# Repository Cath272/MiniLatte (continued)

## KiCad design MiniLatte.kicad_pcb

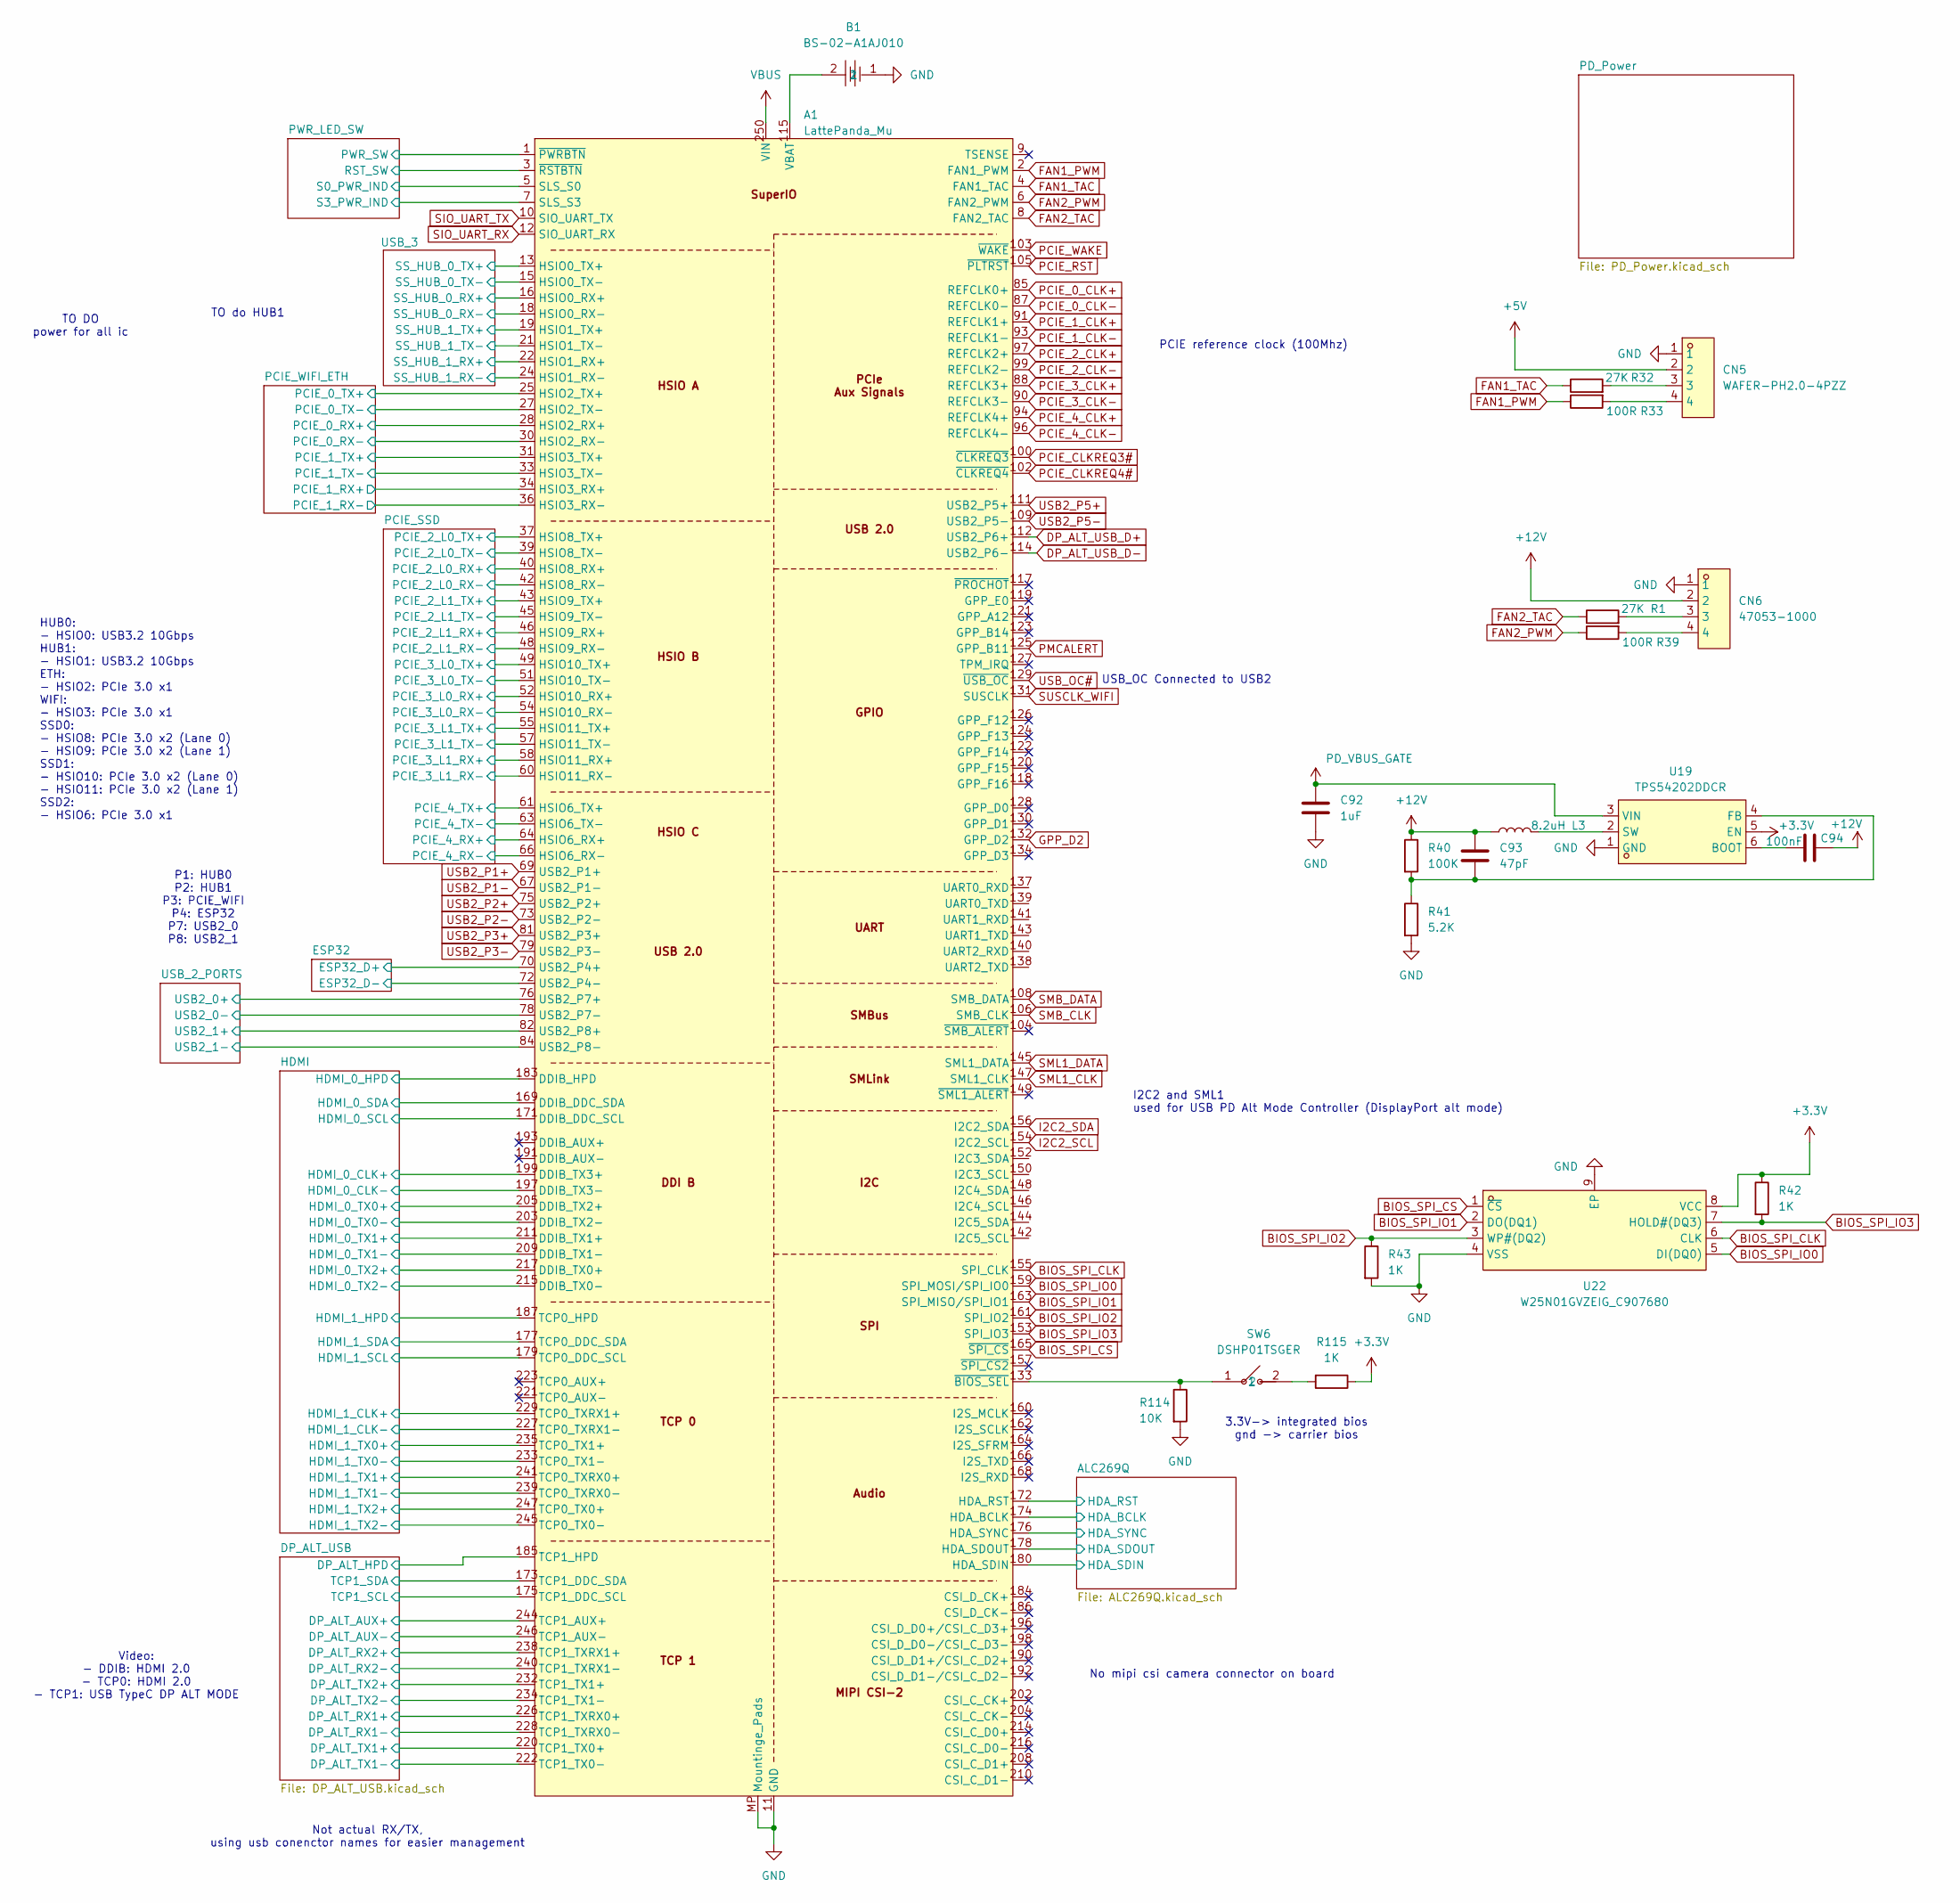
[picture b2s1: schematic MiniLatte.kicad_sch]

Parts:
A1: LattePanda_Mu; LattePanda_Module_H8.0mm_Horizontal
B1: BS-02-A1AJ010; BAT-TH_BS-02-A1AJ010; LCSC Part C5239862
C92: 1uF; C_0603_1608Metric
C93: 47pF; C_0402_1005Metric
C94: 100nF; C_0402_1005Metric
CN5: WAFER-PH2.0-4PZZ; CONN-TH_4P-P2.00_FWF20001-S04S22W5B; LCSC Part C5359601
CN6: 47053-1000; CONN-TH_47053-1000; LCSC Part C240840
L3: 8.2uH; L_Changjiang_FXL0420
R1, R32: 27K; R_0402_1005Metric
R33, R39: 100R; R_0402_1005Metric
R40: 100K; R_0402_1005Metric
R41: 5.2K; R_0402_1005Metric
R42, R43, R115: 1K; R_0402_1005Metric
R114: 10K; R_0402_1005Metric
SW6: DSHP01TSGER; SW-SMD_DSHP01TSGER; LCSC Part C3293141
U19: TPS54202DDCR; SOT-23-6_L2.9-W1.6-P0.95-LS2.8-BL; LCSC Part C191884
U22: W25N01GVZEIG_C907680; WSON-8_L8.0-W6.10-P1.27-BL-EP; LCSC Part C907680

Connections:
+3.3V: R42.1, R115.1, U19.5 (EN), U22.8 (VCC); also elsewhere on the board
+5V: CN5.2; also elsewhere on the board
+12V: C93.1, C94.2, CN6.2, L3.1, R40.1
/ALC269Q/HDA_BCLK: A1.174 (HDA_BCLK); also elsewhere on the board
/ALC269Q/HDA_RST: A1.172 (HDA_RST); also elsewhere on the board
/ALC269Q/HDA_SDIN: A1.180 (HDA_SDIN); also elsewhere on the board
/ALC269Q/HDA_SDOUT: A1.178 (HDA_SDOUT); also elsewhere on the board
/ALC269Q/HDA_SYNC: A1.176 (HDA_SYNC); also elsewhere on the board
/DP_ALT_USB/DP_ALT_HPD: A1.185 (TCP1_HPD); also elsewhere on the board
/DP_ALT_USB/DP_ALT_RX1+: A1.226 (TCP1_TXRX0+); also elsewhere on the board
/DP_ALT_USB/DP_ALT_RX1-: A1.228 (TCP1_TXRX0-); also elsewhere on the board
/DP_ALT_USB/DP_ALT_RX2+: A1.238 (TCP1_TXRX1+); also elsewhere on the board
/DP_ALT_USB/DP_ALT_RX2-: A1.240 (TCP1_TXRX1-); also elsewhere on the board
/DP_ALT_USB/DP_ALT_TX1+: A1.220 (TCP1_TX0+); also elsewhere on the board
/DP_ALT_USB/DP_ALT_TX1-: A1.222 (TCP1_TX0-); also elsewhere on the board
/DP_ALT_USB/DP_ALT_TX2+: A1.232 (TCP1_TX1+); also elsewhere on the board
/DP_ALT_USB/DP_ALT_TX2-: A1.234 (TCP1_TX1-); also elsewhere on the board
/DP_ALT_USB/SBU1: A1.244 (TCP1_AUX+); also elsewhere on the board
/DP_ALT_USB/SBU2: A1.246 (TCP1_AUX-); also elsewhere on the board
/DP_ALT_USB/TCP1_SCL: A1.175 (TCP1_DDC_SCL); also elsewhere on the board
/DP_ALT_USB/TCP1_SDA: A1.173 (TCP1_DDC_SDA); also elsewhere on the board
/ESP32/ESP32_D+: A1.70 (USB2_P4+); also elsewhere on the board
/ESP32/ESP32_D-: A1.72 (USB2_P4-); also elsewhere on the board
/HDMI/HDMI_0_CLK+: A1.199 (DDIB_TX3+); also elsewhere on the board
/HDMI/HDMI_0_CLK-: A1.197 (DDIB_TX3-); also elsewhere on the board
/HDMI/HDMI_0_HPD: A1.183 (DDIB_HPD); also elsewhere on the board
/HDMI/HDMI_0_SCL: A1.171 (DDIB_DDC_SCL); also elsewhere on the board
/HDMI/HDMI_0_SDA: A1.169 (DDIB_DDC_SDA); also elsewhere on the board
/HDMI/HDMI_0_TX0+: A1.205 (DDIB_TX2+); also elsewhere on the board
/HDMI/HDMI_0_TX0-: A1.203 (DDIB_TX2-); also elsewhere on the board
/HDMI/HDMI_0_TX1+: A1.211 (DDIB_TX1+); also elsewhere on the board
/HDMI/HDMI_0_TX1-: A1.209 (DDIB_TX1-); also elsewhere on the board
/HDMI/HDMI_0_TX2+: A1.217 (DDIB_TX0+); also elsewhere on the board
/HDMI/HDMI_0_TX2-: A1.215 (DDIB_TX0-); also elsewhere on the board
/HDMI/HDMI_1_CLK+: A1.229 (TCP0_TXRX1+); also elsewhere on the board
/HDMI/HDMI_1_CLK-: A1.227 (TCP0_TXRX1-); also elsewhere on the board
/HDMI/HDMI_1_HPD: A1.187 (TCP0_HPD); also elsewhere on the board
/HDMI/HDMI_1_SCL: A1.179 (TCP0_DDC_SCL); also elsewhere on the board
/HDMI/HDMI_1_SDA: A1.177 (TCP0_DDC_SDA); also elsewhere on the board
/HDMI/HDMI_1_TX0+: A1.235 (TCP0_TX1+); also elsewhere on the board
/HDMI/HDMI_1_TX0-: A1.233 (TCP0_TX1-); also elsewhere on the board
/HDMI/HDMI_1_TX1+: A1.241 (TCP0_TXRX0+); also elsewhere on the board
/HDMI/HDMI_1_TX1-: A1.239 (TCP0_TXRX0-); also elsewhere on the board
/HDMI/HDMI_1_TX2+: A1.247 (TCP0_TX0+); also elsewhere on the board
/HDMI/HDMI_1_TX2-: A1.245 (TCP0_TX0-); also elsewhere on the board
/PCIE_SSD/PCIE_2_L0_RX+: A1.40 (HSIO8_RX+); also elsewhere on the board
/PCIE_SSD/PCIE_2_L0_RX-: A1.42 (HSIO8_RX-); also elsewhere on the board
/PCIE_SSD/PCIE_2_L0_TX+: A1.37 (HSIO8_TX+); also elsewhere on the board
/PCIE_SSD/PCIE_2_L0_TX-: A1.39 (HSIO8_TX-); also elsewhere on the board
/PCIE_SSD/PCIE_2_L1_RX+: A1.46 (HSIO9_RX+); also elsewhere on the board
/PCIE_SSD/PCIE_2_L1_RX-: A1.48 (HSIO9_RX-); also elsewhere on the board
/PCIE_SSD/PCIE_2_L1_TX+: A1.43 (HSIO9_TX+); also elsewhere on the board
/PCIE_SSD/PCIE_2_L1_TX-: A1.45 (HSIO9_TX-); also elsewhere on the board
/PCIE_SSD/PCIE_3_L0_RX+: A1.52 (HSIO10_RX+); also elsewhere on the board
/PCIE_SSD/PCIE_3_L0_RX-: A1.54 (HSIO10_RX-); also elsewhere on the board
/PCIE_SSD/PCIE_3_L0_TX+: A1.49 (HSIO10_TX+); also elsewhere on the board
/PCIE_SSD/PCIE_3_L0_TX-: A1.51 (HSIO10_TX-); also elsewhere on the board
/PCIE_SSD/PCIE_3_L1_RX+: A1.58 (HSIO11_RX+); also elsewhere on the board
/PCIE_SSD/PCIE_3_L1_RX-: A1.60 (HSIO11_RX-); also elsewhere on the board
/PCIE_SSD/PCIE_3_L1_TX+: A1.55 (HSIO11_TX+); also elsewhere on the board
/PCIE_SSD/PCIE_3_L1_TX-: A1.57 (HSIO11_TX-); also elsewhere on the board
/PCIE_SSD/PCIE_4_RX+: A1.64 (HSIO6_RX+); also elsewhere on the board
/PCIE_SSD/PCIE_4_RX-: A1.66 (HSIO6_RX-); also elsewhere on the board
/PCIE_SSD/PCIE_4_TX+: A1.61 (HSIO6_TX+); also elsewhere on the board
/PCIE_SSD/PCIE_4_TX-: A1.63 (HSIO6_TX-); also elsewhere on the board
/PCIE_WIFI_ETH/PCIE_0_RX+: A1.28 (HSIO2_RX+); also elsewhere on the board
/PCIE_WIFI_ETH/PCIE_0_RX-: A1.30 (HSIO2_RX-); also elsewhere on the board
/PCIE_WIFI_ETH/PCIE_0_TX+: A1.25 (HSIO2_TX+); also elsewhere on the board
/PCIE_WIFI_ETH/PCIE_0_TX-: A1.27 (HSIO2_TX-); also elsewhere on the board
/PCIE_WIFI_ETH/PCIE_1_RX+: A1.34 (HSIO3_RX+); also elsewhere on the board
/PCIE_WIFI_ETH/PCIE_1_RX-: A1.36 (HSIO3_RX-); also elsewhere on the board
/PCIE_WIFI_ETH/PCIE_1_TX+: A1.31 (HSIO3_TX+); also elsewhere on the board
/PCIE_WIFI_ETH/PCIE_1_TX-: A1.33 (HSIO3_TX-); also elsewhere on the board
/PWR_LED_SW/PWR_SW: A1.1 (~PWRBTN); also elsewhere on the board
/PWR_LED_SW/RST_SW: A1.3 (~RSTBTN); also elsewhere on the board
/PWR_LED_SW/S0_PWR_IND: A1.5 (SLS_S0); also elsewhere on the board
/PWR_LED_SW/S3_PWR_IND: A1.7 (SLS_S3); also elsewhere on the board
/USB_2_PORTS/USB2_0+: A1.76 (USB2_P7+); also elsewhere on the board
/USB_2_PORTS/USB2_0-: A1.78 (USB2_P7-); also elsewhere on the board
/USB_2_PORTS/USB2_1+: A1.82 (USB2_P8+); also elsewhere on the board
/USB_2_PORTS/USB2_1-: A1.84 (USB2_P8-); also elsewhere on the board
/USB_3/SS_HUB_0_RX+: A1.16 (HSIO0_RX+); also elsewhere on the board
/USB_3/SS_HUB_0_RX-: A1.18 (HSIO0_RX-); also elsewhere on the board
/USB_3/SS_HUB_0_TX+: A1.13 (HSIO0_TX+); also elsewhere on the board
/USB_3/SS_HUB_0_TX-: A1.15 (HSIO0_TX-); also elsewhere on the board
/USB_3/SS_HUB_1_RX+: A1.22 (HSIO1_RX+); also elsewhere on the board
/USB_3/SS_HUB_1_RX-: A1.24 (HSIO1_RX-); also elsewhere on the board
/USB_3/SS_HUB_1_TX+: A1.19 (HSIO1_TX+); also elsewhere on the board
/USB_3/SS_HUB_1_TX-: A1.21 (HSIO1_TX-); also elsewhere on the board
BIOS_SPI_CLK: A1.155 (SPI_CLK), U22.6 (CLK)
BIOS_SPI_CS: A1.165 (~SPI_CS), U22.1 (~CS)
BIOS_SPI_IO0: A1.159 (SPI_MOSI/SPI_IO0), U22.5 (DI(DQ0))
BIOS_SPI_IO1: A1.163 (SPI_MISO/SPI_IO1), U22.2 (DO(DQ1))
BIOS_SPI_IO2: A1.161 (SPI_IO2), R43.1, U22.3 (WP#(DQ2))
BIOS_SPI_IO3: A1.153 (SPI_IO3), R42.2, U22.7 (HOLD#(DQ3))
DP_ALT_USB_D+: A1.112 (USB2_P6+); also elsewhere on the board
DP_ALT_USB_D-: A1.114 (USB2_P6-); also elsewhere on the board
FAN1_PWM: A1.2 (FAN1_PWM), R33.1
FAN1_TAC: A1.4 (FAN1_TAC), R32.1
FAN2_PWM: A1.6 (FAN2_PWM), R39.1
FAN2_TAC: A1.8 (FAN2_TAC), R1.1
GND: A1.11 (GND), A1.14 (GND), A1.17 (GND), A1.20 (GND), A1.23 (GND), A1.26 (GND), A1.29 (GND), A1.32 (GND), A1.35 (GND), A1.38 (GND), A1.41 (GND), A1.44 (GND), A1.47 (GND), A1.50 (GND), A1.53 (GND), A1.56 (GND), A1.59 (GND), A1.62 (GND), A1.65 (GND), A1.68 (GND), A1.71 (GND), A1.74 (GND), A1.77 (GND), A1.80 (GND), A1.83 (GND), A1.86 (GND), A1.89 (GND), A1.92 (GND), A1.95 (GND), A1.98 (GND), A1.101 (GND), A1.107 (GND), A1.110 (GND), A1.113 (GND), A1.116 (GND), A1.135 (GND), A1.136 (GND), A1.151 (GND), A1.158 (GND), A1.167 (GND), A1.170 (GND), A1.181 (GND), A1.182 (GND), A1.188 (GND), A1.189 (GND), A1.194 (GND), A1.195 (GND), A1.200 (GND), A1.201 (GND), A1.206 (GND), A1.207 (GND), A1.212 (GND), A1.213 (GND), A1.218 (GND), A1.219 (GND), A1.224 (GND), A1.225 (GND), A1.230 (GND), A1.231 (GND), A1.236 (GND), A1.237 (GND), A1.242 (GND), A1.243 (GND), A1.248 (GND), A1.249 (GND), A1.MP (Mountinge_Pads), B1.1, C92.2, CN5.1, CN6.1, R41.2, R43.2, R114.2, U19.1 (GND), U22.4 (VSS), U22.9 (EP); also elsewhere on the board
GPP_D2: A1.132 (GPP_D2); also elsewhere on the board
I2C2_SCL: A1.154 (I2C2_SCL); also elsewhere on the board
I2C2_SDA: A1.156 (I2C2_SDA); also elsewhere on the board
unnamed: A1.115 (VBAT), B1.2
unnamed: A1.133 (~BIOS_SEL), R114.1, SW6.1
unnamed: CN5.3, R32.2
unnamed: CN5.4, R33.2
unnamed: CN6.3, R1.2
unnamed: CN6.4, R39.2
unnamed: R115.2, SW6.2
unnamed: C94.1, U19.6 (BOOT)
unnamed: C93.2, R40.2, R41.1, U19.4 (FB)
unnamed: L3.2, U19.2 (SW)
PCIE_0_CLK+: A1.85 (REFCLK0+); also elsewhere on the board
PCIE_0_CLK-: A1.87 (REFCLK0-); also elsewhere on the board
PCIE_1_CLK+: A1.91 (REFCLK1+); also elsewhere on the board
PCIE_1_CLK-: A1.93 (REFCLK1-); also elsewhere on the board
PCIE_2_CLK+: A1.97 (REFCLK2+); also elsewhere on the board
PCIE_2_CLK-: A1.99 (REFCLK2-); also elsewhere on the board
PCIE_3_CLK+: A1.88 (REFCLK3+); also elsewhere on the board
PCIE_3_CLK-: A1.90 (REFCLK3-); also elsewhere on the board
PCIE_4_CLK+: A1.94 (REFCLK4+); also elsewhere on the board
PCIE_4_CLK-: A1.96 (REFCLK4-); also elsewhere on the board
PCIE_CLKREQ3#: A1.100 (~CLKREQ3); also elsewhere on the board
PCIE_CLKREQ4#: A1.102 (~CLKREQ4); also elsewhere on the board
PCIE_RST: A1.105 (~PLTRST); also elsewhere on the board
PCIE_WAKE: A1.103 (~WAKE); also elsewhere on the board
PD_VBUS_GATE: C92.1, U19.3 (VIN); also elsewhere on the board
PMCALERT: A1.125 (GPP_B11); also elsewhere on the board
SIO_UART_RX: A1.12 (SIO_UART_RX)
SIO_UART_TX: A1.10 (SIO_UART_TX)
SMB_CLK: A1.106 (SMB_CLK)
SMB_DATA: A1.108 (SMB_DATA)
SML1_CLK: A1.147 (SML1_CLK); also elsewhere on the board
SML1_DATA: A1.145 (SML1_DATA); also elsewhere on the board
SUSCLK_WIFI: A1.131 (SUSCLK); also elsewhere on the board
USB2_P1+: A1.69 (USB2_P1+); also elsewhere on the board
USB2_P1-: A1.67 (USB2_P1-); also elsewhere on the board
USB2_P2+: A1.75 (USB2_P2+); also elsewhere on the board
USB2_P2-: A1.73 (USB2_P2-); also elsewhere on the board
USB2_P3+: A1.81 (USB2_P3+); also elsewhere on the board
USB2_P3-: A1.79 (USB2_P3-); also elsewhere on the board
USB2_P5+: A1.111 (USB2_P5+)
USB2_P5-: A1.109 (USB2_P5-)
USB_OC#: A1.129 (~USB_OC); also elsewhere on the board
VBUS: A1.250 (VIN), A1.251 (VIN), A1.252 (VIN), A1.253 (VIN), A1.254 (VIN), A1.255 (VIN), A1.256 (VIN), A1.257 (VIN), A1.258 (VIN), A1.259 (VIN), A1.260 (VIN)

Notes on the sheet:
TO do HUB1
USB_OC Connected to USB2
I2C2 and SML1 used for USB PD Alt Mode Controller (DisplayPort alt mode)
Not actual RX/TX, using usb conenctor names for easier management
TO DO power for all ic
P1: HUB0 P2: HUB1 P3: PCIE_WIFI P4: ESP32 P7: USB2_0 P8: USB2_1
No mipi csi camera connector on board
3.3V-> integrated bios gnd -> carrier bios
PCIE reference clock (100Mhz)
HUB0: - HSIO0: USB3.2 10Gbps HUB1: - HSIO1: USB3.2 10Gbps ETH: - HSIO2: PCIe 3.0 x1 WIFI: - HSIO3: PCIe 3.0 x1 SSD0: - HSIO8: PCIe 3.0 x2 (Lane 0) - HSIO9: PCIe 3.0 x2 (Lane 1) SSD1: - HSIO10: PCIe 3.0 x2 (Lane 0) - HSIO11: PCIe 3.0 x2 (Lane 1) SSD2: - HSIO6: PCIe 3.0 x1
Video: - DDIB: HDMI 2.0 - TCP0: HDMI 2.0 - TCP1: USB TypeC DP ALT MODE

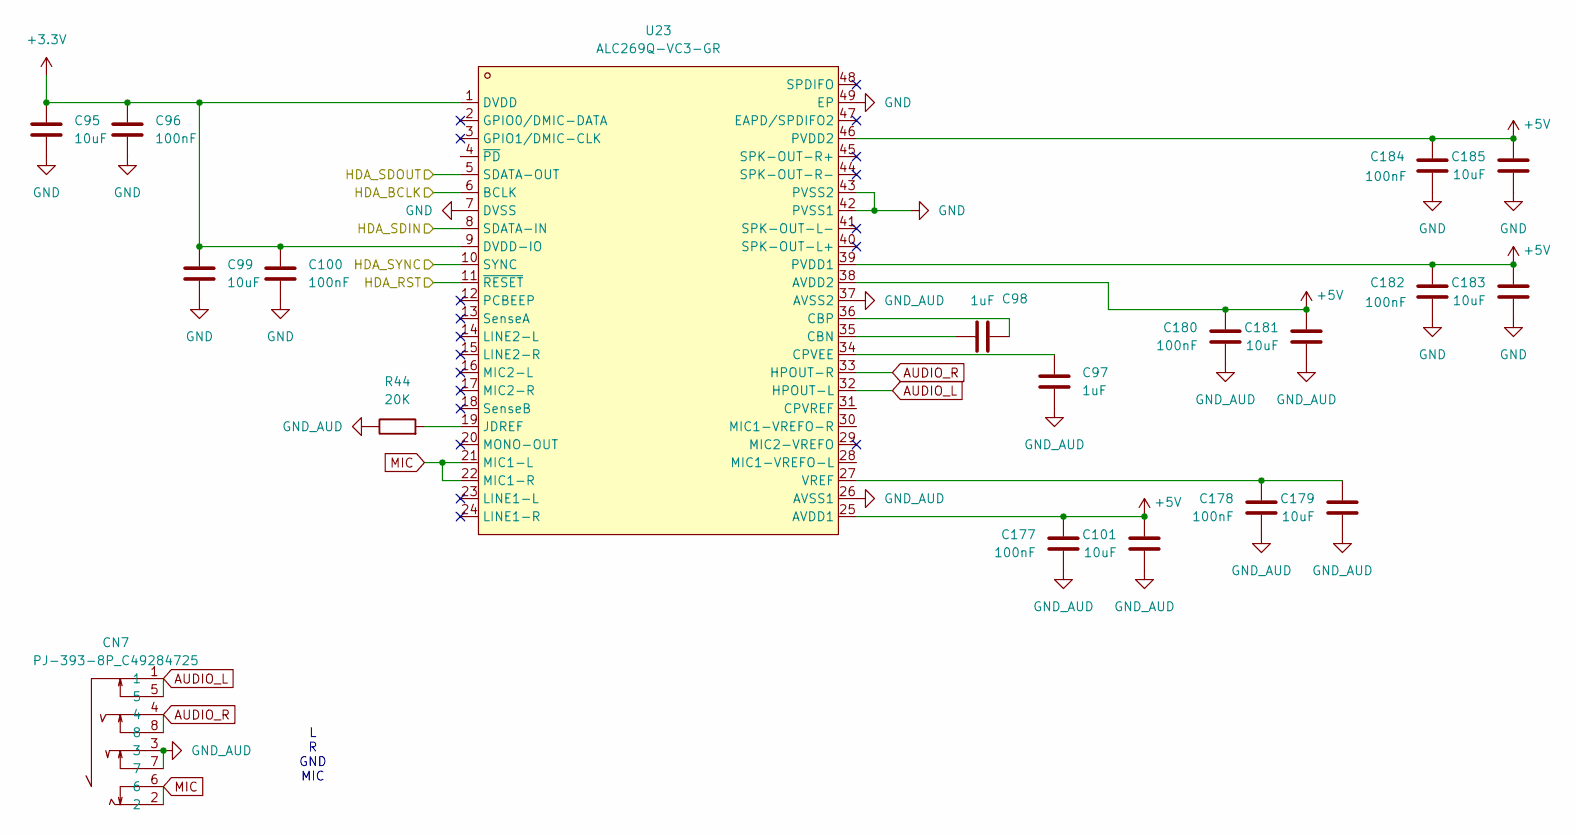
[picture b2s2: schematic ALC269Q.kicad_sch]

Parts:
C95, C99, C101, C179, C181, C183, C185: 10uF; C_0805_2012Metric
C96, C100, C177, C178, C180, C182, C184: 100nF; C_0402_1005Metric
C97, C98: 1uF; C_0603_1608Metric
CN7: PJ-393-8P_C49284725; AUDIO-TH_PJ-393-8P; LCSC Part C49284725
R44: 20K; R_0402_1005Metric
U23: ALC269Q-VC3-GR; QFN-48_L7.0-W7.0-P0.50-BL-EP5.3; LCSC Part C669848

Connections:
+3.3V: C95.1, C96.1, C99.1, C100.1, U23.1 (DVDD), U23.9 (DVDD-IO); also elsewhere on the board
+5V: C101.1, C177.1, C180.1, C181.1, C182.1, C183.1, C184.1, C185.1, U23.25 (AVDD1), U23.38 (AVDD2), U23.39 (PVDD1), U23.46 (PVDD2); also elsewhere on the board
/ALC269Q/HDA_BCLK: U23.6 (BCLK); also elsewhere on the board
/ALC269Q/HDA_RST: U23.11 (~RESET); also elsewhere on the board
/ALC269Q/HDA_SDIN: U23.8 (SDATA-IN); also elsewhere on the board
/ALC269Q/HDA_SDOUT: U23.5 (SDATA-OUT); also elsewhere on the board
/ALC269Q/HDA_SYNC: U23.10 (SYNC); also elsewhere on the board
AUDIO_L: CN7.1, CN7.5, U23.32 (HPOUT-L)
AUDIO_R: CN7.4, CN7.8, U23.33 (HPOUT-R)
GND: C95.2, C96.2, C99.2, C100.2, C182.2, C183.2, C184.2, C185.2, U23.7 (DVSS), U23.42 (PVSS1), U23.43 (PVSS2), U23.49 (EP); also elsewhere on the board
GND_AUD: C97.2, C101.2, C177.2, C178.2, C179.2, C180.2, C181.2, CN7.3, CN7.7, R44.1, U23.26 (AVSS1), U23.37 (AVSS2)
MIC: CN7.2, CN7.6, U23.21 (MIC1-L), U23.22 (MIC1-R)
unnamed: C98.1, U23.35 (CBN)
unnamed: C98.2, U23.36 (CBP)
unnamed: C97.1, U23.34 (CPVEE)
unnamed: R44.2, U23.19 (JDREF)
unnamed: C178.1, C179.1, U23.27 (VREF)

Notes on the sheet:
L R GND MIC

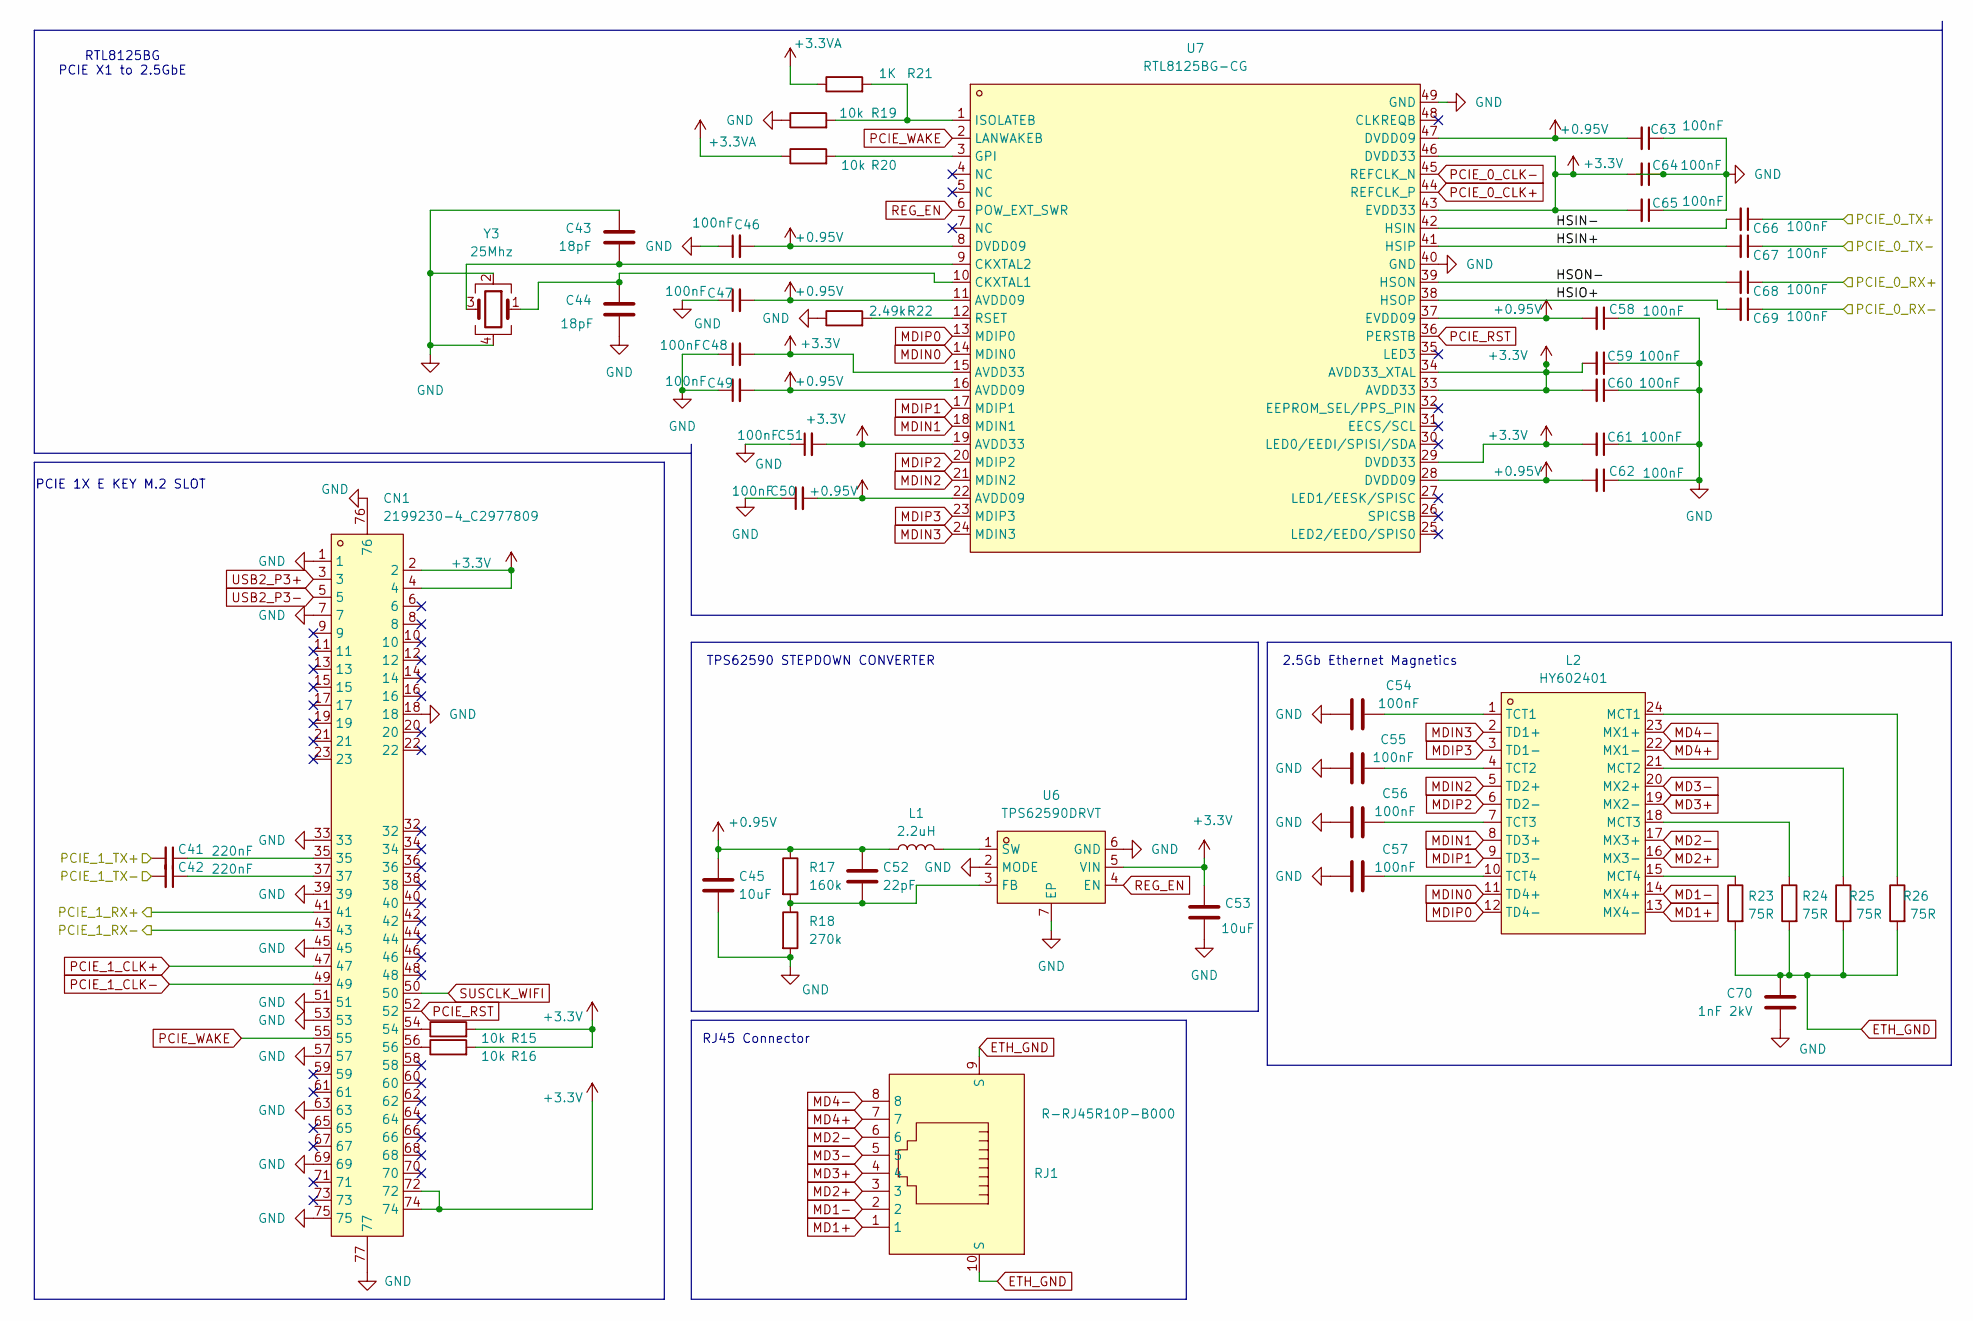
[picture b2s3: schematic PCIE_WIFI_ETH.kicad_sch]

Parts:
C41, C42: 220nF; C_0402_1005Metric
C43, C44: 18pF; C_0402_1005Metric
C45, C53: 10uF; C_0805_2012Metric
C46, C47, C48, C49, C50, C51, C54, C55, C56, C57, C58, C59, C60, C61, C62, C63, C64, C65, C66, C67, C68, C69: 100nF; C_0402_1005Metric
C52: 22pF; C_0402_1005Metric
C70: 1nF 2kV; C_1210_3225Metric
CN1: 2199230-4_C2977809; PCIE-SMD_2199230-4; LCSC Part C2977809
L1: 2.2uH; IND-SMD_L3.5-W3.0
L2: HY602401; XFMR-SMD_HY602401; LCSC Part C55685
R15, R16, R19, R20: 10k; R_0402_1005Metric
R17: 160k; R_0402_1005Metric
R18: 270k; R_0402_1005Metric
R21: 1K; R_0402_1005Metric
R22: 2.49k; R_0402_1005Metric
R23, R24, R25, R26: 75R; R_0402_1005Metric
RJ1: R-RJ45R10P-B000; RJ45-TH_R-RJ45R10P-B000; LCSC Part C386758
U6: TPS62590DRVT; WSON-6_L2.0-W2.0-P0.65-TL-EP; LCSC Part C2862349
U7: RTL8125BG-CG; TQFN-48_L6.0-W6.0-P0.40-BL-EP4.5; LCSC Part C3013605
Y3: 25Mhz; Crystal_SMD_3225-4Pin_3.2x2.5mm

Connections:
+0.95V: C45.1, C46.2, C47.2, C49.2, C50.2, C52.1, C58.2, C62.2, C63.2, L1.1, R17.1, U7.8 (DVDD09), U7.11 (AVDD09), U7.16 (AVDD09), U7.22 (AVDD09), U7.28 (DVDD09), U7.37 (EVDD09), U7.47 (DVDD09)
+3.3V: C48.2, C51.2, C53.1, C59.2, C60.2, C61.2, C64.2, C65.2, CN1.2, CN1.4, CN1.72, CN1.74, R15.2, R16.2, U6.5 (VIN), U7.15 (AVDD33), U7.19 (AVDD33), U7.29 (DVDD33), U7.33 (AVDD33), U7.34 (AVDD33_XTAL), U7.43 (EVDD33), U7.46 (DVDD33); also elsewhere on the board
+3.3VA: R20.1, R21.1
/PCIE_WIFI_ETH/HSIN+: C67.2, U7.41 (HSIP)
/PCIE_WIFI_ETH/HSIN-: C66.2, U7.42 (HSIN)
/PCIE_WIFI_ETH/HSIO+: C69.2, U7.38 (HSOP)
/PCIE_WIFI_ETH/HSON-: C68.2, U7.39 (HSON)
/PCIE_WIFI_ETH/PCIE_0_RX+: C68.1; also elsewhere on the board
/PCIE_WIFI_ETH/PCIE_0_RX-: C69.1; also elsewhere on the board
/PCIE_WIFI_ETH/PCIE_0_TX+: C66.1; also elsewhere on the board
/PCIE_WIFI_ETH/PCIE_0_TX-: C67.1; also elsewhere on the board
/PCIE_WIFI_ETH/PCIE_1_RX+: CN1.41; also elsewhere on the board
/PCIE_WIFI_ETH/PCIE_1_RX-: CN1.43; also elsewhere on the board
/PCIE_WIFI_ETH/PCIE_1_TX+: C41.2; also elsewhere on the board
/PCIE_WIFI_ETH/PCIE_1_TX-: C42.2; also elsewhere on the board
ETH_GND: C70.1, R23.2, R24.2, R25.2, R26.2, RJ1.9 (S), RJ1.10 (S)
GND: C43.1, C44.2, C45.2, C46.1, C47.1, C48.1, C49.1, C50.1, C51.1, C53.2, C54.2, C55.2, C56.2, C57.2, C58.1, C59.1, C60.1, C61.1, C62.1, C63.1, C64.1, C65.1, C70.2, CN1.1, CN1.7, CN1.18, CN1.33, CN1.39, CN1.45, CN1.51, CN1.53, CN1.57, CN1.63, CN1.69, CN1.75, CN1.76, CN1.77, R18.2, R19.1, R22.1, U6.2 (MODE), U6.6 (GND), U6.7 (EP), U7.40 (GND), U7.49 (GND), Y3.2, Y3.4; also elsewhere on the board
MD1+: L2.13 (MX4-), RJ1.1
MD1-: L2.14 (MX4+), RJ1.2
MD2+: L2.16 (MX3-), RJ1.3
MD2-: L2.17 (MX3+), RJ1.6
MD3+: L2.19 (MX2-), RJ1.4
MD3-: L2.20 (MX2+), RJ1.5
MD4+: L2.22 (MX1-), RJ1.7
MD4-: L2.23 (MX1+), RJ1.8
MDIN0: L2.11 (TD4+), U7.14 (MDIN0)
MDIN1: L2.8 (TD3+), U7.18 (MDIN1)
MDIN2: L2.5 (TD2+), U7.21 (MDIN2)
MDIN3: L2.2 (TD1+), U7.24 (MDIN3)
MDIP0: L2.12 (TD4-), U7.13 (MDIP0)
MDIP1: L2.9 (TD3-), U7.17 (MDIP1)
MDIP2: L2.6 (TD2-), U7.20 (MDIP2)
MDIP3: L2.3 (TD1-), U7.23 (MDIP3)
unnamed: C41.1, CN1.35
unnamed: C42.1, CN1.37
unnamed: CN1.54, R15.1
unnamed: CN1.56, R16.1
unnamed: L2.24 (MCT1), R26.1
unnamed: L2.21 (MCT2), R25.1
unnamed: L2.18 (MCT3), R24.1
unnamed: L2.15 (MCT4), R23.1
unnamed: C54.1, L2.1 (TCT1)
unnamed: C55.1, L2.4 (TCT2)
unnamed: C56.1, L2.7 (TCT3)
unnamed: C57.1, L2.10 (TCT4)
unnamed: C52.2, R17.2, R18.1, U6.3 (FB)
unnamed: L1.2, U6.1 (SW)
unnamed: C44.1, U7.10 (CKXTAL1), Y3.1
unnamed: C43.2, U7.9 (CKXTAL2), Y3.3
unnamed: R20.2, U7.3 (GPI)
unnamed: R19.2, R21.2, U7.1 (ISOLATEB)
unnamed: R22.2, U7.12 (RSET)
PCIE_0_CLK+: U7.44 (REFCLK_P); also elsewhere on the board
PCIE_0_CLK-: U7.45 (REFCLK_N); also elsewhere on the board
PCIE_1_CLK+: CN1.47; also elsewhere on the board
PCIE_1_CLK-: CN1.49; also elsewhere on the board
PCIE_RST: CN1.52, U7.36 (PERSTB); also elsewhere on the board
PCIE_WAKE: CN1.55, U7.2 (LANWAKEB); also elsewhere on the board
REG_EN: U6.4 (EN), U7.6 (POW_EXT_SWR)
SUSCLK_WIFI: CN1.50; also elsewhere on the board
USB2_P3+: CN1.3; also elsewhere on the board
USB2_P3-: CN1.5; also elsewhere on the board

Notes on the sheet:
TPS62590 STEPDOWN CONVERTER
RTL8125BG PCIE X1 to 2.5GbE
PCIE 1X E KEY M.2 SLOT
2.5Gb Ethernet Magnetics
RJ45 Connector

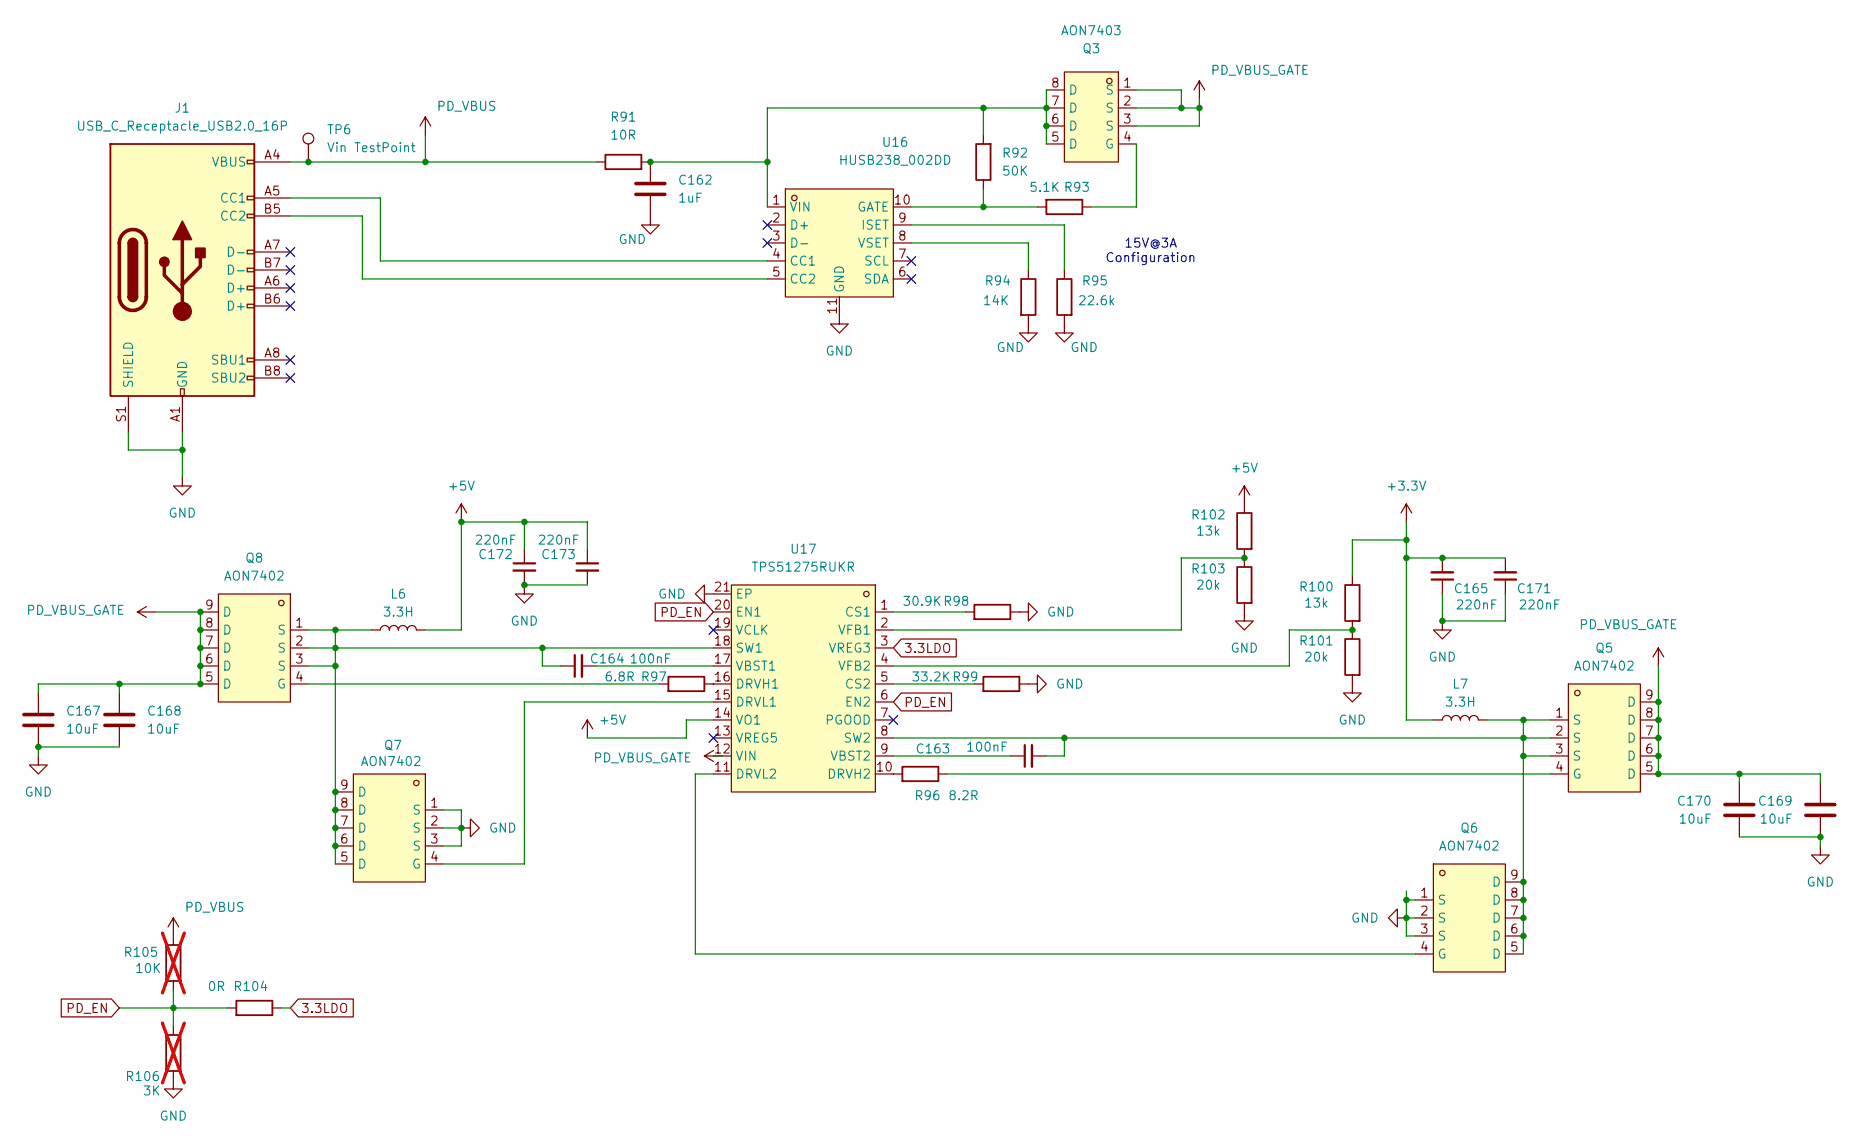
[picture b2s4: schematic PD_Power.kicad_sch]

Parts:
C162: 1uF; C_0603_1608Metric
C163, C164: 100nF; C_0402_1005Metric
C165, C171, C172, C173: 220nF; C_0402_1005Metric
C167, C168, C169, C170: 10uF; C_0805_2012Metric
J1: USB_C_Receptacle_USB2.0_16P; USB_C_Receptacle_GCT_USB4105-xx-A_16P_TopMnt_Horizontal
L6, L7: 3.3H; L_APV_APH1040
Q3: AON7403; PQFN-8_L3.1-W3.1-P0.65-LS3.3-BL; LCSC Part C115841
Q5, Q6, Q7, Q8: AON7402; PDFN-8_L3.1-W3.1-P0.65-LS3.4-BL; LCSC Part C2925732
R91: 10R; R_0402_1005Metric
R92: 50K; R_0402_1005Metric
R93: 5.1K; R_0402_1005Metric
R94: 14K; R_0402_1005Metric
R95: 22.6k; R_0402_1005Metric
R96: 8.2R; R_0402_1005Metric
R97: 6.8R; R_0402_1005Metric
R98: 30.9K; R_0402_1005Metric
R99: 33.2K; R_0402_1005Metric
R100, R102: 13k; R_0402_1005Metric
R101, R103: 20k; R_0402_1005Metric
R104: 0R; R_0402_1005Metric
R105: 10K; R_0402_1005Metric; not fitted
R106: 3K; R_0402_1005Metric; not fitted
TP6: Vin TestPoint; TestPoint_Pad_2.0x2.0mm
U16: HUSB238_002DD; DFN-10_L3.0-W3.0-P0.50-BL-EP2.5; LCSC Part C7471904
U17: TPS51275RUKR; WQFN-20_L3.0-W3.0-P0.40-BL-EP1.7; LCSC Part C544917

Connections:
3.3LDO: R104.1, U17.3 (VREG3)
+3.3V: C165.2, C171.2, L7.1, R100.1; also elsewhere on the board
+5V: C172.1, C173.1, L6.2, R102.1, U17.14 (VO1); also elsewhere on the board
GND: C162.2, C165.1, C167.2, C168.2, C169.2, C170.2, C171.1, C172.2, C173.2, J1.A1 (GND), J1.A12 (GND), J1.B1 (GND), J1.B12 (GND), J1.S1 (SHIELD), Q6.1 (S), Q6.2 (S), Q6.3 (S), Q7.1 (S), Q7.2 (S), Q7.3 (S), R94.2, R95.2, R98.1, R99.1, R101.2, R103.2, R106.2, U16.11 (GND), U17.21 (EP); also elsewhere on the board
unnamed: J1.A5 (CC1), U16.4 (CC1)
unnamed: J1.B5 (CC2), U16.5 (CC2)
unnamed: Q3.4 (G), R93.1
unnamed: Q5.4 (G), R96.1
unnamed: Q6.4 (G), U17.11 (DRVL2)
unnamed: Q7.4 (G), U17.15 (DRVL1)
unnamed: Q8.4 (G), R97.2
unnamed: R92.1, R93.2, U16.10 (GATE)
unnamed: R95.1, U16.9 (ISET)
unnamed: C162.1, Q3.5 (D), Q3.6 (D), Q3.7 (D), Q3.8 (D), R91.2, R92.2, U16.1 (VIN)
unnamed: R94.1, U16.8 (VSET)
unnamed: R98.2, U17.1 (CS1)
unnamed: R99.2, U17.5 (CS2)
unnamed: R97.1, U17.16 (DRVH1)
unnamed: R96.2, U17.10 (DRVH2)
unnamed: C164.1, L6.1, Q7.5 (D), Q7.6 (D), Q7.7 (D), Q7.8 (D), Q7.9 (D), Q8.1 (S), Q8.2 (S), Q8.3 (S), U17.18 (SW1)
unnamed: C163.2, L7.2, Q5.1 (S), Q5.2 (S), Q5.3 (S), Q6.5 (D), Q6.6 (D), Q6.7 (D), Q6.8 (D), Q6.9 (D), U17.8 (SW2)
unnamed: C164.2, U17.17 (VBST1)
unnamed: C163.1, U17.9 (VBST2)
unnamed: R102.2, R103.1, U17.2 (VFB1)
unnamed: R100.2, R101.1, U17.4 (VFB2)
PD_EN: R104.2, R105.2, R106.1, U17.6 (EN2), U17.20 (EN1)
PD_VBUS: J1.A4 (VBUS), J1.A9 (VBUS), J1.B4 (VBUS), J1.B9 (VBUS), R91.1, R105.1, TP6.1
PD_VBUS_GATE: C167.1, C168.1, C169.1, C170.1, Q3.1 (S), Q3.2 (S), Q3.3 (S), Q5.5 (D), Q5.6 (D), Q5.7 (D), Q5.8 (D), Q5.9 (D), Q8.5 (D), Q8.6 (D), Q8.7 (D), Q8.8 (D), Q8.9 (D), U17.12 (VIN); also elsewhere on the board

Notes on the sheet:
15V@3A Configuration
